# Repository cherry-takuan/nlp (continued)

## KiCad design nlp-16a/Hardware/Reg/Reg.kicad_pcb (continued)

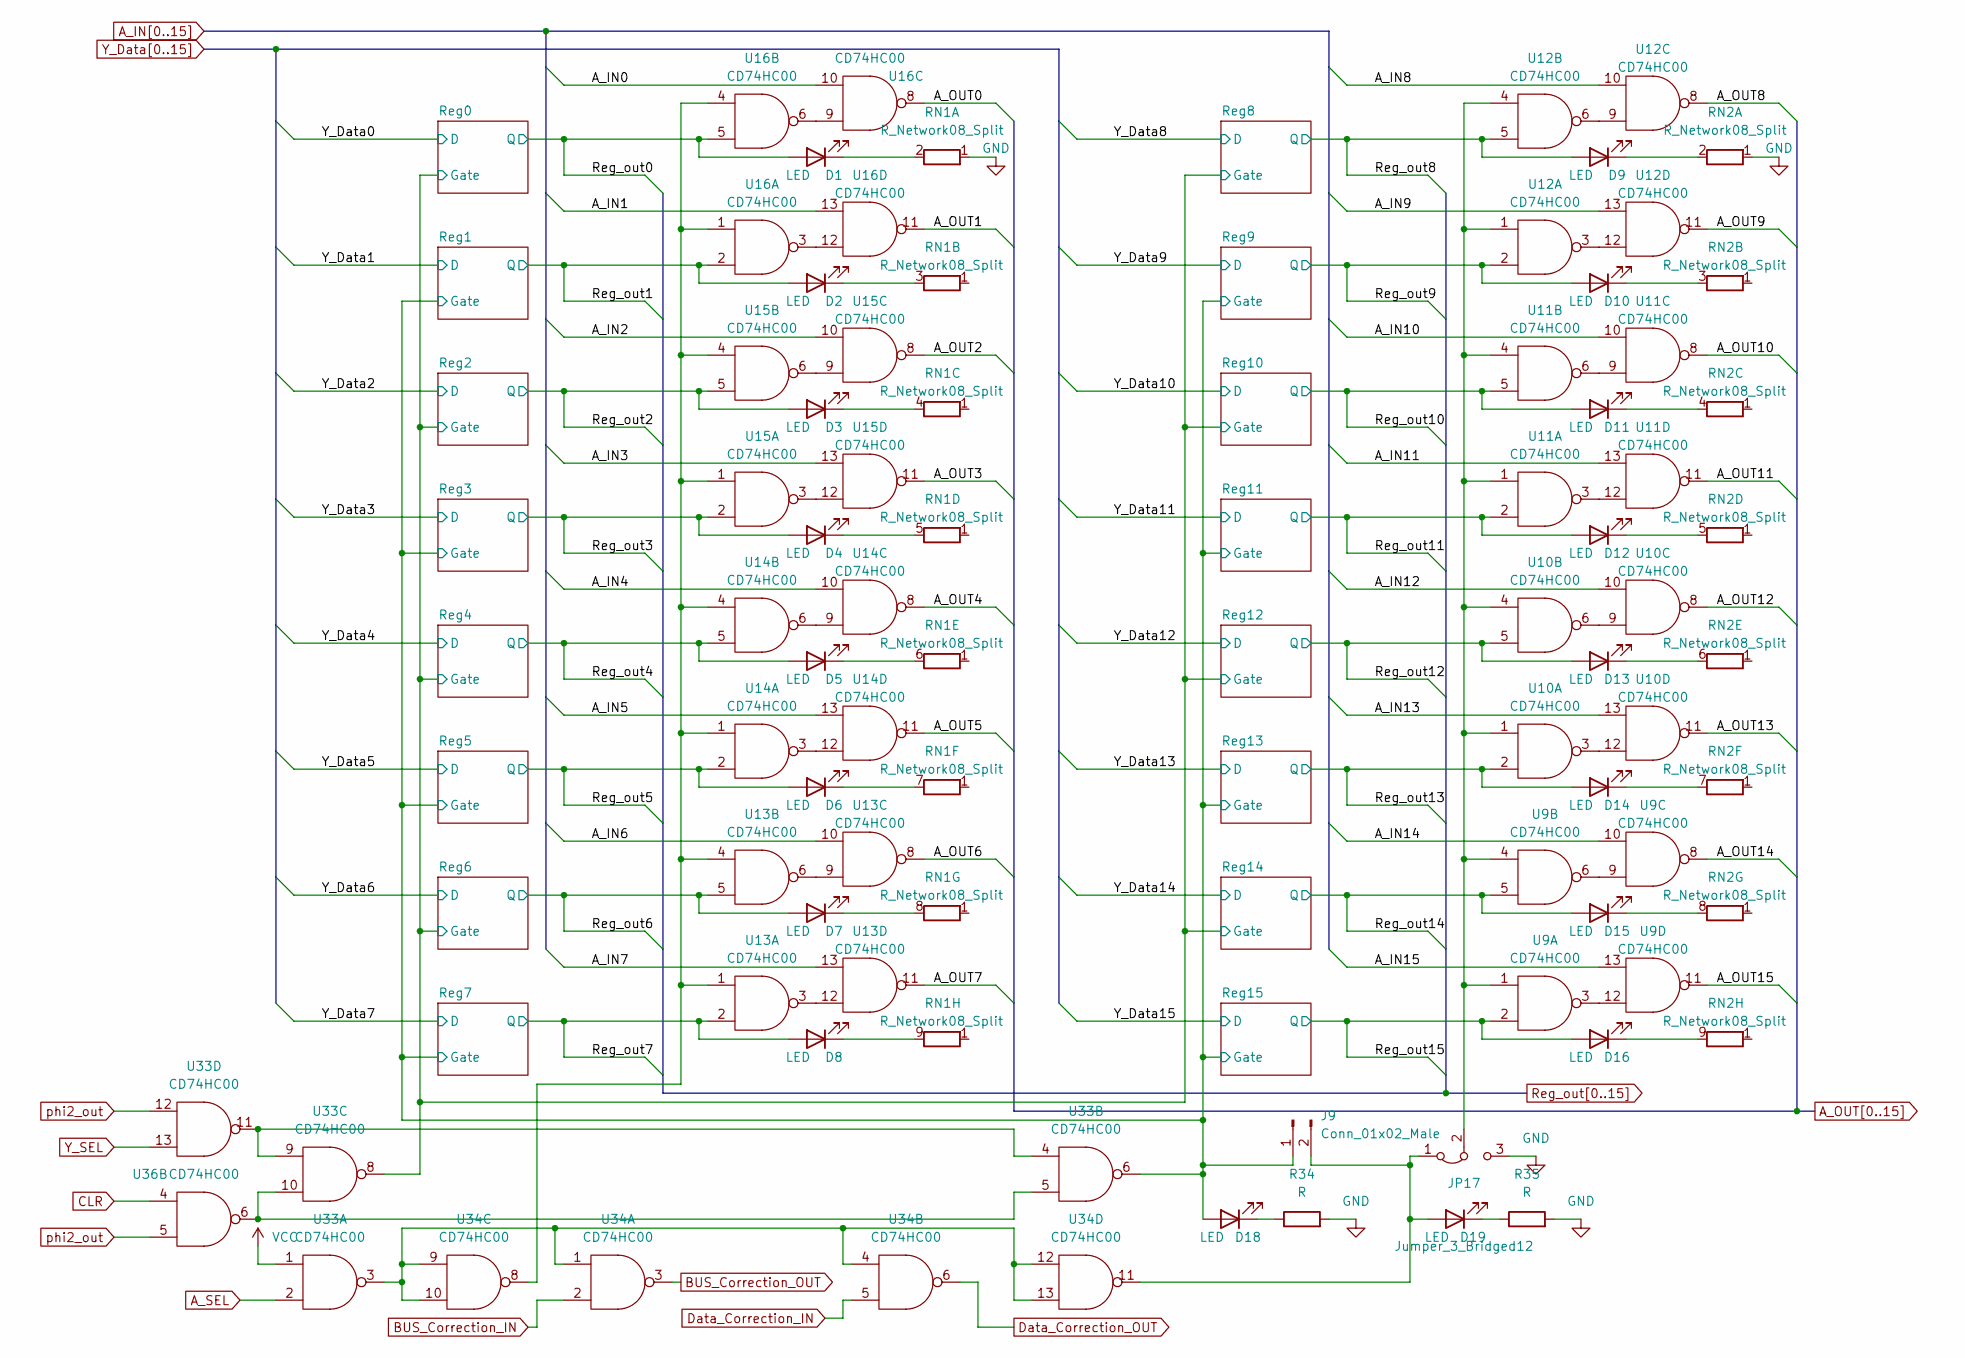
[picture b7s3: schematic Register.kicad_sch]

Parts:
D1, D2, D3, D4, D5, D6, D7, D8, D9, D10, D11, D12, D13, D14, D15, D16, D18, D19: LED; LED_D3.0mm
J9: Conn_01x02_Male; PinHeader_1x02_P2.54mm_Horizontal
JP17: Jumper_3_Bridged12; SolderJumper-3_P1.3mm_Bridged12_RoundedPad1.0x1.5mm_NumberL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
R34, R35: R; R_0603_1608Metric_Pad0.98x0.95mm_HandSolder
RN1, RN2: R_Network08_Split; R_Array_SIP9
U9, U10, U11, U12, U13, U14, U15, U16, U33, U34, U36: CD74HC00; DIP-14_W7.62mm

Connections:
/Register/Reg0/Gate: U33.8; also elsewhere on the board
/Register/Reg1/Gate: D18.2 (A), J9.1, U33.6; also elsewhere on the board
A_IN0: U16.10; also elsewhere on the board
A_IN1: U16.13; also elsewhere on the board
A_IN2: U15.10; also elsewhere on the board
A_IN3: U15.13; also elsewhere on the board
A_IN4: U14.10; also elsewhere on the board
A_IN5: U14.13; also elsewhere on the board
A_IN6: U13.10; also elsewhere on the board
A_IN7: U13.13; also elsewhere on the board
A_IN8: U12.10; also elsewhere on the board
A_IN9: U12.13; also elsewhere on the board
A_IN10: U11.10; also elsewhere on the board
A_IN11: U11.13; also elsewhere on the board
A_IN12: U10.10; also elsewhere on the board
A_IN13: U10.13; also elsewhere on the board
A_IN14: U9.10; also elsewhere on the board
A_IN15: U9.13; also elsewhere on the board
A_OUT0: U16.8; also elsewhere on the board
A_OUT1: U16.11; also elsewhere on the board
A_OUT2: U15.8; also elsewhere on the board
A_OUT3: U15.11; also elsewhere on the board
A_OUT4: U14.8; also elsewhere on the board
A_OUT5: U14.11; also elsewhere on the board
A_OUT6: U13.8; also elsewhere on the board
A_OUT7: U13.11; also elsewhere on the board
A_OUT8: U12.8; also elsewhere on the board
A_OUT9: U12.11; also elsewhere on the board
A_OUT10: U11.8; also elsewhere on the board
A_OUT11: U11.11; also elsewhere on the board
A_OUT12: U10.8; also elsewhere on the board
A_OUT13: U10.11; also elsewhere on the board
A_OUT14: U9.8; also elsewhere on the board
A_OUT15: U9.11; also elsewhere on the board
A_SEL: U33.2; also elsewhere on the board
BUS_Correction_IN: U34.2; also elsewhere on the board
BUS_Correction_OUT: U34.3; also elsewhere on the board
CLR: U36.4; also elsewhere on the board
Data_Correction_IN: U34.5; also elsewhere on the board
Data_Correction_OUT: U34.6; also elsewhere on the board
GND: JP17.3 (B), R34.2, R35.2, RN1.1 (R1.1), RN2.1 (R1.1), U9.7 (GND), U10.7 (GND), U11.7 (GND), U12.7 (GND), U13.7 (GND), U14.7 (GND), U15.7 (GND), U16.7 (GND), U33.7 (GND), U34.7 (GND), U36.7 (GND); also elsewhere on the board
unnamed: D1.1 (K), RN1.2 (R1.2)
unnamed: D2.1 (K), RN1.3 (R2.2)
unnamed: D3.1 (K), RN1.4 (R3.2)
unnamed: D4.1 (K), RN1.5 (R4.2)
unnamed: D5.1 (K), RN1.6 (R5.2)
unnamed: D6.1 (K), RN1.7 (R6.2)
unnamed: D7.1 (K), RN1.8 (R7.2)
unnamed: D8.1 (K), RN1.9 (R8.2)
unnamed: D9.1 (K), RN2.2 (R1.2)
unnamed: D10.1 (K), RN2.3 (R2.2)
unnamed: D11.1 (K), RN2.4 (R3.2)
unnamed: D12.1 (K), RN2.5 (R4.2)
unnamed: D13.1 (K), RN2.6 (R5.2)
unnamed: D14.1 (K), RN2.7 (R6.2)
unnamed: D15.1 (K), RN2.8 (R7.2)
unnamed: D16.1 (K), RN2.9 (R8.2)
unnamed: D18.1 (K), R34.1
unnamed: D19.1 (K), R35.1
unnamed: D19.2 (A), J9.2, JP17.1 (A), U34.11
unnamed: JP17.2 (C), U9.1, U9.4, U10.1, U10.4, U11.1, U11.4, U12.1, U12.4
unnamed: U9.6, U9.9
unnamed: U9.3, U9.12
unnamed: U10.6, U10.9
unnamed: U10.3, U10.12
unnamed: U11.6, U11.9
unnamed: U11.3, U11.12
unnamed: U12.6, U12.9
unnamed: U12.3, U12.12
unnamed: U13.1, U13.4, U14.1, U14.4, U15.1, U15.4, U16.1, U16.4, U34.8
unnamed: U13.6, U13.9
unnamed: U13.3, U13.12
unnamed: U14.6, U14.9
unnamed: U14.3, U14.12
unnamed: U15.6, U15.9
unnamed: U15.3, U15.12
unnamed: U16.6, U16.9
unnamed: U16.3, U16.12
unnamed: U33.3, U34.1, U34.4, U34.9, U34.10, U34.12, U34.13
unnamed: U33.5, U33.10, U36.6
unnamed: U33.4, U33.9, U33.11
Reg_out0: D1.2 (A), U16.5; also elsewhere on the board
Reg_out1: D2.2 (A), U16.2; also elsewhere on the board
Reg_out2: D3.2 (A), U15.5; also elsewhere on the board
Reg_out3: D4.2 (A), U15.2; also elsewhere on the board
Reg_out4: D5.2 (A), U14.5; also elsewhere on the board
Reg_out5: D6.2 (A), U14.2; also elsewhere on the board
Reg_out6: D7.2 (A), U13.5; also elsewhere on the board
Reg_out7: D8.2 (A), U13.2; also elsewhere on the board
Reg_out8: D9.2 (A), U12.5; also elsewhere on the board
Reg_out9: D10.2 (A), U12.2; also elsewhere on the board
Reg_out10: D11.2 (A), U11.5; also elsewhere on the board
Reg_out11: D12.2 (A), U11.2; also elsewhere on the board
Reg_out12: D13.2 (A), U10.5; also elsewhere on the board
Reg_out13: D14.2 (A), U10.2; also elsewhere on the board
Reg_out14: D15.2 (A), U9.5; also elsewhere on the board
Reg_out15: D16.2 (A), U9.2; also elsewhere on the board
VCC: U9.14 (VCC), U10.14 (VCC), U11.14 (VCC), U12.14 (VCC), U13.14 (VCC), U14.14 (VCC), U15.14 (VCC), U16.14 (VCC), U33.1, U33.14 (VCC), U34.14 (VCC), U36.14 (VCC); also elsewhere on the board
Y_SEL: U33.13; also elsewhere on the board
phi2_out: U33.12, U36.5; also elsewhere on the board

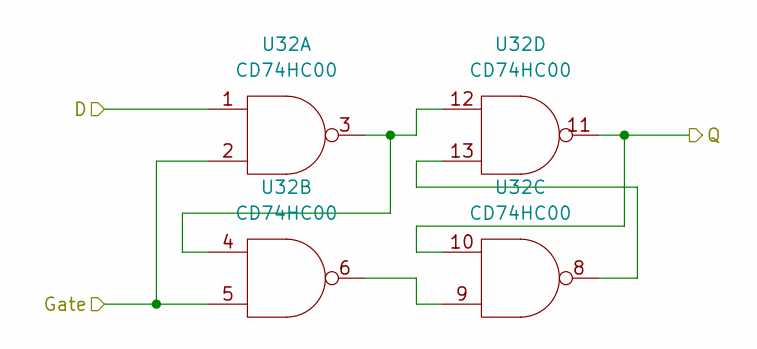
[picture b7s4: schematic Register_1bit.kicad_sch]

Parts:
U32: CD74HC00; DIP-14_W7.62mm

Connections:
/Register/Reg0/Gate: U32.2, U32.5; also elsewhere on the board
GND: U32.7 (GND); also elsewhere on the board
unnamed: U32.6, U32.9
unnamed: U32.3, U32.4, U32.12
unnamed: U32.8, U32.13
Reg_out0: U32.10, U32.11; also elsewhere on the board
VCC: U32.14 (VCC); also elsewhere on the board
Y_Data0: U32.1; also elsewhere on the board

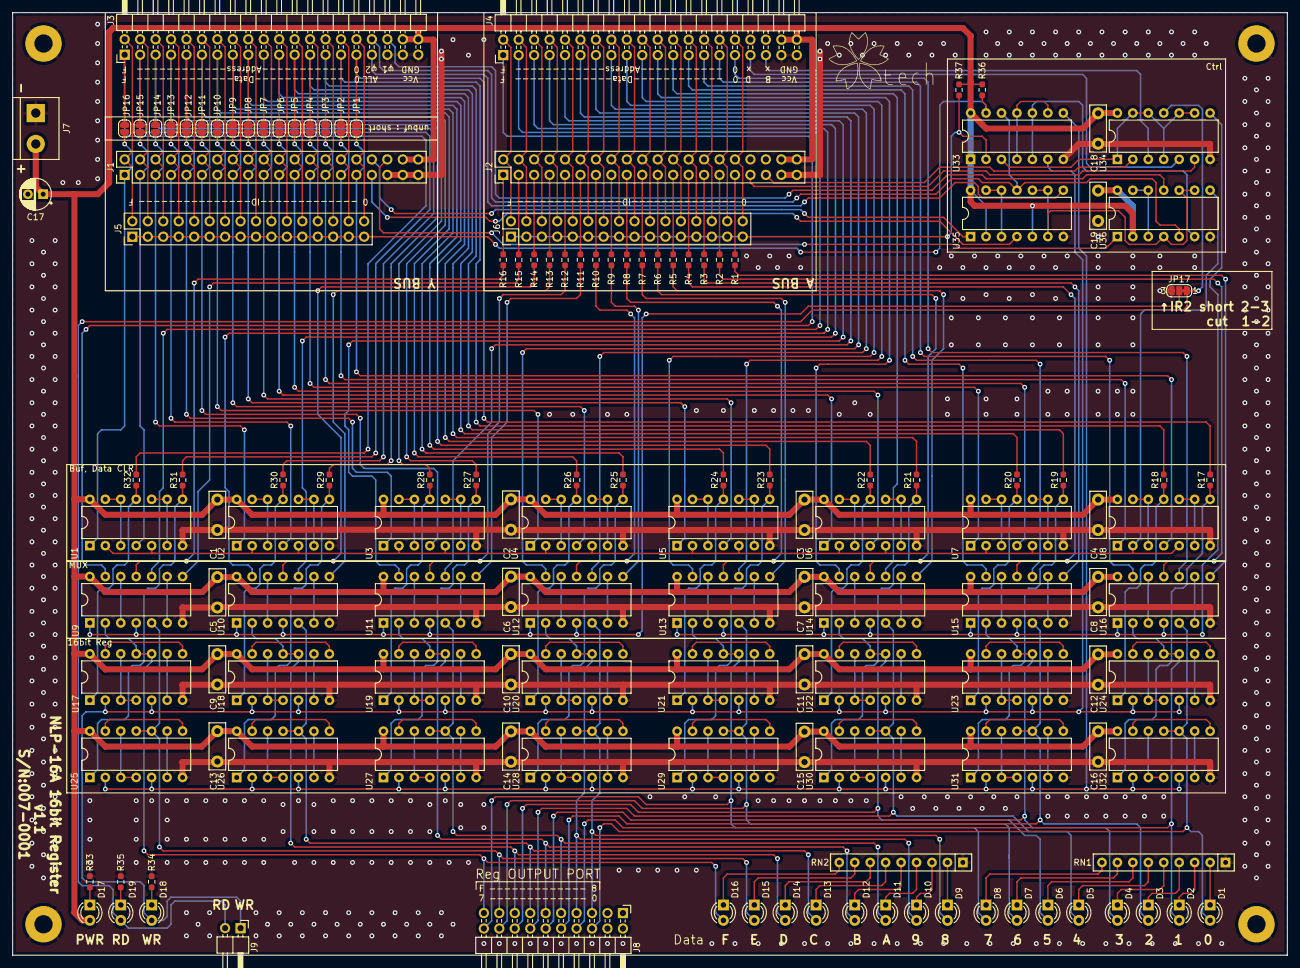
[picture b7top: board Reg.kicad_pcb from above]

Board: 2 copper layers, 209.6 x 154.9 mm, 143 parts (0 on the bottom side), 269 nets.

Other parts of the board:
U17, U18, U19, U20, U21, U22, U23, U24, U25, U26, U27, U28, U29, U30, U31: CD74HC00; DIP-14_W7.62mm

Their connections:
/Register/Reg0/Gate: U25.2, U25.5, U26.2, U26.5, U27.2, U27.5, U28.2, U28.5, U29.2, U29.5, U30.2, U30.5, U31.2, U31.5; also elsewhere on the board
/Register/Reg1/Gate: U17.2, U17.5, U18.2, U18.5, U19.2, U19.5, U20.2, U20.5, U21.2, U21.5, U22.2, U22.5, U23.2, U23.5, U24.2, U24.5; also elsewhere on the board
GND: U17.7 (GND), U18.7 (GND), U19.7 (GND), U20.7 (GND), U21.7 (GND), U22.7 (GND), U23.7 (GND), U24.7 (GND), U25.7 (GND), U26.7 (GND), U27.7 (GND), U28.7 (GND), U29.7 (GND), U30.7 (GND), U31.7 (GND); also elsewhere on the board
unnamed: U17.6, U17.9
unnamed: U17.3, U17.4, U17.12
unnamed: U17.8, U17.13
unnamed: U18.6, U18.9
unnamed: U18.3, U18.4, U18.12
unnamed: U18.8, U18.13
unnamed: U19.6, U19.9
unnamed: U19.3, U19.4, U19.12
unnamed: U19.8, U19.13
unnamed: U20.6, U20.9
unnamed: U20.3, U20.4, U20.12
unnamed: U20.8, U20.13
unnamed: U21.6, U21.9
unnamed: U21.3, U21.4, U21.12
unnamed: U21.8, U21.13
unnamed: U22.6, U22.9
unnamed: U22.3, U22.4, U22.12
unnamed: U22.8, U22.13
unnamed: U23.6, U23.9
unnamed: U23.3, U23.4, U23.12
unnamed: U23.8, U23.13
unnamed: U24.6, U24.9
unnamed: U24.3, U24.4, U24.12
unnamed: U24.8, U24.13
unnamed: U25.6, U25.9
unnamed: U25.3, U25.4, U25.12
unnamed: U25.8, U25.13
unnamed: U26.6, U26.9
unnamed: U26.3, U26.4, U26.12
unnamed: U26.8, U26.13
unnamed: U27.6, U27.9
unnamed: U27.3, U27.4, U27.12
unnamed: U27.8, U27.13
unnamed: U28.6, U28.9
unnamed: U28.3, U28.4, U28.12
unnamed: U28.8, U28.13
unnamed: U29.6, U29.9
unnamed: U29.3, U29.4, U29.12
unnamed: U29.8, U29.13
unnamed: U30.6, U30.9
unnamed: U30.3, U30.4, U30.12
unnamed: U30.8, U30.13
unnamed: U31.6, U31.9
unnamed: U31.3, U31.4, U31.12
unnamed: U31.8, U31.13
Reg_out1: U24.10, U24.11; also elsewhere on the board
Reg_out2: U31.10, U31.11; also elsewhere on the board
Reg_out3: U23.10, U23.11; also elsewhere on the board
Reg_out4: U30.10, U30.11; also elsewhere on the board
Reg_out5: U22.10, U22.11; also elsewhere on the board
Reg_out6: U29.10, U29.11; also elsewhere on the board
Reg_out7: U21.10, U21.11; also elsewhere on the board
Reg_out8: U28.10, U28.11; also elsewhere on the board
Reg_out9: U20.10, U20.11; also elsewhere on the board
Reg_out10: U27.10, U27.11; also elsewhere on the board
Reg_out11: U19.10, U19.11; also elsewhere on the board
Reg_out12: U26.10, U26.11; also elsewhere on the board
Reg_out13: U18.10, U18.11; also elsewhere on the board
Reg_out14: U25.10, U25.11; also elsewhere on the board
Reg_out15: U17.10, U17.11; also elsewhere on the board
VCC: U17.14 (VCC), U18.14 (VCC), U19.14 (VCC), U20.14 (VCC), U21.14 (VCC), U22.14 (VCC), U23.14 (VCC), U24.14 (VCC), U25.14 (VCC), U26.14 (VCC), U27.14 (VCC), U28.14 (VCC), U29.14 (VCC), U30.14 (VCC), U31.14 (VCC); also elsewhere on the board
Y_Data1: U24.1; also elsewhere on the board
Y_Data2: U31.1; also elsewhere on the board
Y_Data3: U23.1; also elsewhere on the board
Y_Data4: U30.1; also elsewhere on the board
Y_Data5: U22.1; also elsewhere on the board
Y_Data6: U29.1; also elsewhere on the board
Y_Data7: U21.1; also elsewhere on the board
Y_Data8: U28.1; also elsewhere on the board
Y_Data9: U20.1; also elsewhere on the board
Y_Data10: U27.1; also elsewhere on the board
Y_Data11: U19.1; also elsewhere on the board
Y_Data12: U26.1; also elsewhere on the board
Y_Data13: U18.1; also elsewhere on the board
Y_Data14: U25.1; also elsewhere on the board
Y_Data15: U17.1; also elsewhere on the board

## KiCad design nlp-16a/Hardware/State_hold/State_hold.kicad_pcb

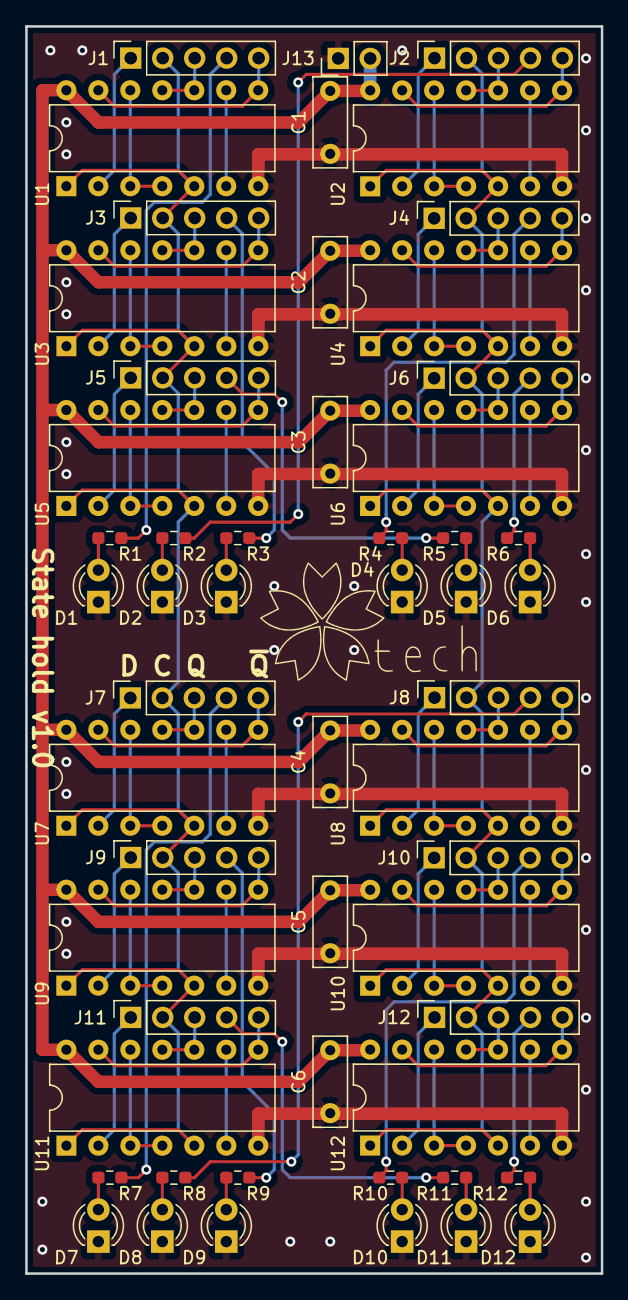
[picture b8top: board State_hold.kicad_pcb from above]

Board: 2 copper layers, 45.7 x 99.1 mm, 55 parts (0 on the bottom side), 88 nets.

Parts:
C1, C2, C3, C4, C5, C6: C; C_Disc_D7.0mm_W2.5mm_P5.00mm
D1, D2, D3, D4, D5, D6, D7, D8, D9, D10, D11, D12: LED; LED_D3.0mm
J1, J2, J3, J4, J5, J6, J7, J8, J9, J10, J11, J12: Conn_01x05_Female; PinSocket_1x05_P2.54mm_Vertical
J13: Conn_01x02_Male; PinHeader_1x02_P2.54mm_Vertical
R1, R2, R3, R4, R5, R6, R7, R8, R9, R10, R11, R12: R; R_0603_1608Metric_Pad0.98x0.95mm_HandSolder
U1, U2, U3, U4, U5, U6, U7, U8, U9, U10, U11, U12: CD74HC00; DIP-14_W7.62mm

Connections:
/State_latch0/D: J1.1, U1.2
/State_latch0/Gate: J1.2, J3.2, J5.2, J7.2, J9.2, J11.2, U1.1, U1.5, U3.1, U3.5, U5.1, U5.5, U7.1, U7.5, U9.1, U9.5, U11.1, U11.5
/State_latch0/LED: J1.4, R1.1
/State_latch0/Q: J1.3, U1.10, U1.11
/State_latch0/~Q: J1.5, U1.8, U1.13
/State_latch1/D: J2.1, U2.2
/State_latch1/Gate: J2.2, J4.2, J6.2, J8.2, J10.2, J12.2, U2.1, U2.5, U4.1, U4.5, U6.1, U6.5, U8.1, U8.5, U10.1, U10.5, U12.1, U12.5
/State_latch1/LED: J2.4, R2.1
/State_latch1/Q: J2.3, U2.10, U2.11
/State_latch1/~Q: J2.5, U2.8, U2.13
/State_latch2/D: J3.1, U3.2
/State_latch2/LED: J3.4, R3.1
/State_latch2/Q: J3.3, U3.10, U3.11
/State_latch2/~Q: J3.5, U3.8, U3.13
/State_latch3/D: J4.1, U4.2
/State_latch3/LED: J4.4, R4.1
/State_latch3/Q: J4.3, U4.10, U4.11
/State_latch3/~Q: J4.5, U4.8, U4.13
/State_latch4/D: J5.1, U5.2
/State_latch4/LED: J5.4, R5.1
/State_latch4/Q: J5.3, U5.10, U5.11
/State_latch4/~Q: J5.5, U5.8, U5.13
/State_latch5/D: J6.1, U6.2
/State_latch5/LED: J6.4, R6.1
/State_latch5/Q: J6.3, U6.10, U6.11
/State_latch5/~Q: J6.5, U6.8, U6.13
/State_latch6/D: J7.1, U7.2
/State_latch6/LED: J7.4, R7.1
/State_latch6/Q: J7.3, U7.10, U7.11
/State_latch6/~Q: J7.5, U7.8, U7.13
/State_latch7/D: J8.1, U8.2
/State_latch7/LED: J8.4, R8.1
/State_latch7/Q: J8.3, U8.10, U8.11
/State_latch7/~Q: J8.5, U8.8, U8.13
/State_latch8/D: J9.1, U9.2
/State_latch8/LED: J9.4, R9.1
/State_latch8/Q: J9.3, U9.10, U9.11
/State_latch8/~Q: J9.5, U9.8, U9.13
/State_latch9/D: J10.1, U10.2
/State_latch9/LED: J10.4, R10.1
/State_latch9/Q: J10.3, U10.10, U10.11
/State_latch9/~Q: J10.5, U10.8, U10.13
/State_latch10/D: J11.1, U11.2
/State_latch10/LED: J11.4, R11.1
/State_latch10/Q: J11.3, U11.10, U11.11
/State_latch10/~Q: J11.5, U11.8, U11.13
/State_latch11/D: J12.1, U12.2
/State_latch11/LED: J12.4, R12.1
/State_latch11/Q: J12.3, U12.10, U12.11
/State_latch11/~Q: J12.5, U12.8, U12.13
GND: C1.1, C2.1, C3.1, C4.1, C5.1, C6.1, D1.1 (K), D2.1 (K), D3.1 (K), D4.1 (K), D5.1 (K), D6.1 (K), D7.1 (K), D8.1 (K), D9.1 (K), D10.1 (K), D11.1 (K), D12.1 (K), J13.1, U1.7 (GND), U2.7 (GND), U3.7 (GND), U4.7 (GND), U5.7 (GND), U6.7 (GND), U7.7 (GND), U8.7 (GND), U9.7 (GND), U10.7 (GND), U11.7 (GND), U12.7 (GND)
unnamed: D1.2 (A), R1.2
unnamed: D2.2 (A), R2.2
unnamed: D3.2 (A), R3.2
unnamed: D4.2 (A), R4.2
unnamed: D5.2 (A), R5.2
unnamed: D6.2 (A), R6.2
unnamed: D7.2 (A), R7.2
unnamed: D8.2 (A), R8.2
unnamed: D9.2 (A), R9.2
unnamed: D10.2 (A), R10.2
unnamed: D11.2 (A), R11.2
unnamed: D12.2 (A), R12.2
unnamed: U1.6, U1.9
unnamed: U1.3, U1.4, U1.12
unnamed: U2.6, U2.9
unnamed: U2.3, U2.4, U2.12
unnamed: U3.6, U3.9
unnamed: U3.3, U3.4, U3.12
unnamed: U4.6, U4.9
unnamed: U4.3, U4.4, U4.12
unnamed: U5.6, U5.9
unnamed: U5.3, U5.4, U5.12
unnamed: U6.6, U6.9
unnamed: U6.3, U6.4, U6.12
unnamed: U7.6, U7.9
unnamed: U7.3, U7.4, U7.12
unnamed: U8.6, U8.9
unnamed: U8.3, U8.4, U8.12
unnamed: U9.6, U9.9
unnamed: U9.3, U9.4, U9.12
unnamed: U10.6, U10.9
unnamed: U10.3, U10.4, U10.12
unnamed: U11.6, U11.9
unnamed: U11.3, U11.4, U11.12
unnamed: U12.6, U12.9
unnamed: U12.3, U12.4, U12.12
VCC: C1.2, C2.2, C3.2, C4.2, C5.2, C6.2, J13.2, U1.14 (VCC), U2.14 (VCC), U3.14 (VCC), U4.14 (VCC), U5.14 (VCC), U6.14 (VCC), U7.14 (VCC), U8.14 (VCC), U9.14 (VCC), U10.14 (VCC), U11.14 (VCC), U12.14 (VCC)

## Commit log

2023-05-17 NLP-16,Aの説明
2023-05-17 NLP-16説明更新
2023-05-17 NLP-16A説明更新
2023-05-17 readme追加
2023-05-17 readme場所修正
2023-05-17 説明画像
2023-05-17 リネーム
2023-05-17 ALU基板
2023-05-17 説明修正
2023-05-17 タイポ修正
2023-05-17 PNGを除外
2023-06-15 周辺機器RS-232Cの回路図等
2023-06-15 周辺機器RS-232Cのreadme追加
2023-06-18 周辺機器RS-232C,定数および接続ピンの修正
2023-06-29 ALU制御追加
2023-07-14 部品表追加
2023-07-17 ALU制御の回路修正
2023-07-17 ALU基板 ターミナルの干渉を修正
2023-07-17 ALU制御シミュレーション追加
2023-07-17 デコーダ二段目?の0
2023-07-17 デコーダ二段目?の1
2023-07-17 デコーダ二段目?の2
2023-07-17 デコーダ二段目?の3
2023-07-17 デコーダ二段目?の4
2023-07-17 デコーダ二段目?の5
2023-07-17 デコーダ二段目?の6
2023-07-17 デコーダ二段目?の7
2023-07-17 デコーダを合わせたものを追加
2023-07-17 誤字修正
2023-07-17 ゼロフラグ高速化
2023-07-18 基板の途中経過(デコーダ部分を配線中)
2023-07-18 基板の途中経過
2023-07-19 デコーダ周りの配線が通った!
2023-07-19 githubのページから作業が見られるように思いつきで基板，回路のプレビューを追加．以下ではなるべく変更時にプレビューを更新
2023-07-19 電源バス，シルクスクリーン更新
2023-07-19 Ctrlバス表示LED配線
2023-07-19 Yバス他修正
2023-07-19 だいたい終了残りは制御バスのデバッグポートのみ
2023-07-20 ignore修正
2023-07-20 バックアップファイル削除
2023-07-23 コミット漏れていた
2023-07-24 デバッグポート(ALU制御バス)の配置プランが立った
2023-07-24 電源バスの引き直しとデバッグポートの配線完了
2023-07-24 基板プレビュー更新
2023-07-24 だいたい完成．残りは詳細チェックとビア打ち
2023-07-24 ALU制御基板OK
2023-07-25 ロゴを入れた
2023-07-26 オーバーフロー検出部修正
2023-07-26 軽微な回路修正
2023-07-26 基板の発注データ生成
2023-07-26 先ほどのオーバーフロー検出部の不具合を修正
2023-07-26 基板の製造データ生成
2023-07-26 J6，J7の位置を修正
2023-07-26 基板の製造データ生成最終
2023-07-26 最終版基板プレビュー
2023-07-26 最終版ALU
2023-08-21 デバッガ基板
2023-08-21 デバッガのソフト
2023-08-21 デバッガのプレビューPDF追加
2023-08-21 readme更新
2023-08-21 基板修正
2023-08-21 A,Bバスコントローラ
2023-08-22 内部処理モードを追加
2023-08-22 信号補正部追加
2023-08-22 配線作業開始
2023-09-04 デバッガ基板の設計完了
2023-09-04 部品表更新
2023-09-04 デバッガ基板の設計今度こそ完了
2023-09-06 Yバス制御追加
2023-09-06 TMPレジスタ等を追加
2023-09-06 Yバスだいたい配線完了
2023-09-06 YバスTMPRegリファレンス割り当て
2023-09-08 アドレスデコーダ部の論理のミスを修正
2023-09-08 Yバス制御 配置の決定，リファレンスの割り当て，ERCの確認完了
2023-10-02 デバッガ，ALU基板更新
2023-10-02 デバッガ関連ソフト作成
2023-10-02 デバッガテストハード構成画像追加
2023-10-04 ALU制御 右シフト/右ロール機能選択部の不具合を修正
2023-10-27 ALU手動テストボード追加
2023-10-29 見積もり他
2023-10-30 ALU手動テストボード使いやすいように更新
2023-11-12 Y BUS制御の基板をとりあえず描いた．ビアとかはまた後で
2023-11-12 Y BUS制御のpdf追加
2023-11-24 .gitignore追記
2023-11-24 回路，基板PDF
2023-12-06 Y-BUS制御完成
2023-12-06 Acc回路完成(変更の可能性有)
2024-01-11 ワークショップ用資料(仮)
2024-01-14 ワークショップ用資料
2024-01-20 ワークショップ用資料改
2024-01-20 ワークショップリンク掲載
2024-01-24 A BUS制御 更新
2024-01-24 Y BUS制御 更新
2024-01-24 アキュムレータ 更新
2024-01-24 BUSターミネータ 更新
2024-01-25 モニタプログラムのmikubugを追加
2024-01-25 アキュムレータ更新
2024-01-25 バスターミネータ基板製造データ更新
2024-01-27 バスターミネータのWR，RDのクロックを追加
2024-01-27 バスターミネータのDMA機能は不要と判断したので削除．必要ならば外部回路で実現するように
2024-01-31 アプリケーション例追加
2024-02-02 レジスタ基板
2024-02-04 レジスタ基板だいたい完成
2024-02-04 レジスタ回路プレビュー
2024-02-11 テストで見つかった不具合を修正(れジスタアドレスデコーダ，Addrの内部処理の方法を変更)
2024-02-11 テストを受けてレジスタの設計を更新
2024-02-11 レジスタクリア時の動作を修正
2024-02-11 レジスタ製造データ更新
2024-02-15 ALUとデータバスのデバッグ
2024-02-15 画像更新
2024-02-22 偽VTL
2024-02-22 実行ファイル削除
2024-02-22 操作追記
2024-02-22 イロイロ修正
2024-02-25 進捗更新
2024-02-25 Reg更新
2024-02-26 命令セット
2024-02-26 スペルミス
2024-02-26 シフト演算修正
2024-02-26 NOT修正
2024-03-09 ライセンス付け忘れていた
2024-03-09 Flagフィールド改定
2024-03-12 命令デコーダインターフェイスとりあえずコミット
2024-03-12 ハードウェアテストコード類
2024-03-12 Y BUS制御 IV -> Acc ENの修正
2024-03-14 命令デコーダインターフェイスの回路がだいたいおｋ
2024-03-14 A BUS制御 IVとIR3のアドレスの処理変更を反映
2024-03-14 アキュムレータ書き込み条件変更(内部処理モードとAcc選択を追加)
2024-03-14 使用しない基板を削除
2024-03-14 命令デコーダのステート保持用ラッチ追加
2024-03-27 割り込み許可/禁止のニモニックをx86に合わせた
2024-03-30 ステート保持ラッチ再設計．おそらく問題無し
2024-03-31 命令デコーダの回路ひとまず書き出し．未完成
2024-03-31 命令デコーダ 不具合修正
2024-03-31 ALU制御 修正分反映
2024-03-31 命令デコーダとの配線方法を変更
2024-04-07 現在の更新を追記
2024-04-08 命令デコーダ ロジック部の設計だいたい完了git statusgit statusやったぜ
2024-04-08 命令デコーダ 軽微な修正
2024-04-09 コンパイラはじめました
2024-04-21 アノテーションまで完了．基板設計に入る
2024-04-23 基板設計 今日はとりあえずここまで
2024-04-24 基板設計 進捗
2024-05-03 命令デコーダ完了！！
2024-05-03 命令デコーダインターフェイスだいたい完了！！
2024-05-03 軽微な修正を加えてガーバー作成 発注
2024-05-13 Y BUS制御の軽微な修正
2024-05-13 修正はしていないがkicadで開いたら謎に変更が入った
2024-05-13 テスト修正
2024-05-13 命令デコーダのテスト
2024-05-13 CPUにプログラムを転送する
2024-05-13 CPUにプログラムを転送する2
2024-05-13 テストの軽微な修正
2024-05-17 再帰下降構文解析まで．ソースコードの受け取り方も変更した
2024-05-20 ごちうさ演奏プログラム
2024-05-25 作りを変えるので一度セーブポイント
2024-05-25 トークナイザと再帰下降構文解析をがっちゃんこ
2024-05-26 自動テストまでの環境を構築
2024-05-26 テストスクリプト
2024-05-26 comsumeの改良と単項の追加，add()の追加
2024-05-26 比較演算子(== !=)実装
2024-05-26 動作の結果も記録しておく
2024-05-26 >noバグ修正完了
2024-05-26 複数のステートメントに対応
2024-05-26 一文字ローカル変数対応
2024-05-26 一文字ローカル変数テスト．DIVサブルーチンでBP(Reg D)が破壊されている
2024-05-26 MUL/DIVサブルーチンの修正．
2024-05-27 複数文字の変数とreturnに対応
2024-05-27 複数文字とreturnデバッグ
2024-05-27 if文に対応
2024-05-27 複数行のソースのエラー表示に対応
2024-05-27 for文実装
2024-05-27 複文に対応．フィボナッチが動かせるようになった
2024-05-29 とりあえず関数をパースできるようにした(中身はまだ)
2024-07-15 ALU エラッタ修正版
2024-07-15 ALU制御 エラッタ修正版
2024-07-22 A BUS制御修正
2024-07-22 Y BUS制御修正
2024-07-22 アキュムレータ修正
2024-07-22 命令デコーダ修正
2024-08-02 全回路収録PDF
2024-08-04 v1.1全ガーバーを更新
2024-08-13 ALUをデバッグする奴を今の形に更新
2024-08-14 デバッグ更新
2024-08-14 終了処理修正
2024-08-14 Y BUS Accのテスト
2024-08-14 Regのテスト
2024-08-14 終了時常にeixt(1)になってたのを直した
2024-08-16 デバッガのデバッグ
2024-08-26 全体テスト更新
2024-08-26 デバッガ改良
2024-10-04 デバッガファーム(リセット無効)
2024-10-19 周辺ボード追加
2024-10-19 デバッガのガーバー更新
2024-10-29 RAMボードの部品の値を修正
2024-11-02 RAMテストを現在のデバッグ環境に対応
2024-11-02 RAMテストのアドレス指定を修正
2024-11-02 古いコードを除外
2024-11-02 デバッガのファームが古かったので修正
2024-11-02 NLP-16Aテキストエディタ
2024-11-02 テキストエディタの基本的なインターフェイス(挿入，後退，移動)完成
2024-11-02 テキストエディタの軽微な修正
2024-11-02 テキストエディタの基本的な入出力を実装
2024-11-03 行指向の表示
2024-11-03 文字の挿入を実装
2024-11-03 行の削除を実装
2024-11-09 ALUとデータバス関連のテスト
2024-11-09 ALUとデータバス関連のテストID修正
2024-11-16 Y BUS制御リセット端子にプルアップ追加
2024-11-21 MIKBUGを16A+周辺機器ボード用に修正
2024-11-30 MSMP送受信アプリケーション
2024-11-30 MSMP送受信アプリケーションRPN付
2024-11-30 MSMP送受信アプリケーションRPN付完成
2024-11-30 MSMP送受信アプリケーションテスト用のTeratermマクロ
2024-12-01 除算の速度を調べるためのテストを追加
2024-12-03 テストコード修正(今後Addr Regのテストを追加予定)
2024-12-05 命令デコーダテストコード修正
2024-12-05 命令デコーダテスト内容
2024-12-06 円周率計算のアプリケーションを追加
2024-12-06 ライフゲームに軽微な修正
2024-12-06 スタック破壊の修正とモニタからの呼び出しに対応
2024-12-06 RPNを16A用に修正
2024-12-06 サンプルコードリストを修正
2024-12-06 アプリケーションのロードと実行方法を追加
2024-12-06 readme修正
2024-12-27 RPN計算機を負の数値に対応
2024-12-28 マンデルブロ集合実装
2024-12-31 ISAの表を追加
2024-12-31 アーキテクチャの概要
2025-01-13 接続ポートとモニタプログラムの修正
2025-01-26 関数定義を追加
2025-01-26 NLP-16Aエミュレータを導入し，テストを変更
2025-01-26 関数呼び出し対応
2025-02-02 変数の型を明示
2025-02-02 変数定義の位置が違う気がしたので変更
2025-03-01 仕切り直して一旦書き直し ビジュアライザを入れた
2025-03-02 関数と変数の定義
2025-03-02 関数が引数を取れるようにした
2025-03-02 パラメータ付きの関数CALL
2025-03-02 return追加
2025-03-02 logical or andを追加
2025-03-04 ポインタ周りを実装
2025-03-10 前のテストを通るまでには来た
2025-03-10 再帰のプログラム動いた
2025-03-10 一次元配列の宣言とポインタを使ったアクセス
2025-03-11 相対アドレッシング時のレジスタサイズ計算のバグを修正
2025-03-11 配列の実装とエミュレータのデバッグツールを追加
2025-03-11 配列を[]でアクセスできるようにした
2025-03-11 IND/DEC追加
2025-03-11 mod演算と文字出力を追加
2025-03-11 グローバル変数(int)追加
2025-03-11 グローバル変数(array)追加
2025-03-27 キーボード制御ユーティリティ追加
2025-04-11 MALLOC,EXIT,INOPUTnoを追加
2025-04-30 ブロック崩し
2025-05-24 ハードウェアReadme
2025-05-24 ハードウェアReadmeちょっと修正
2025-07-07 アーキテクチャ，命令セットへのリンクを追加
2025-07-07 周辺ボード説明追加
2025-08-10 ASTの画像生成を改良(NULLを無視)
2025-08-10 再帰処理のサンプルとしてハノイの塔をテストに追加
2025-10-11 break/continue追加
2025-10-12 グローバル変数の初期化式を追加
2025-10-13 シフト演算を追加
2025-10-13 ビット演算と論理OR，ANDを修正
